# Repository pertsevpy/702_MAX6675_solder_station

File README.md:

# 702_MAX6675_solder_station
Simple 702 (Hakko 907) soldering station, use ATmega8 and MAX6675

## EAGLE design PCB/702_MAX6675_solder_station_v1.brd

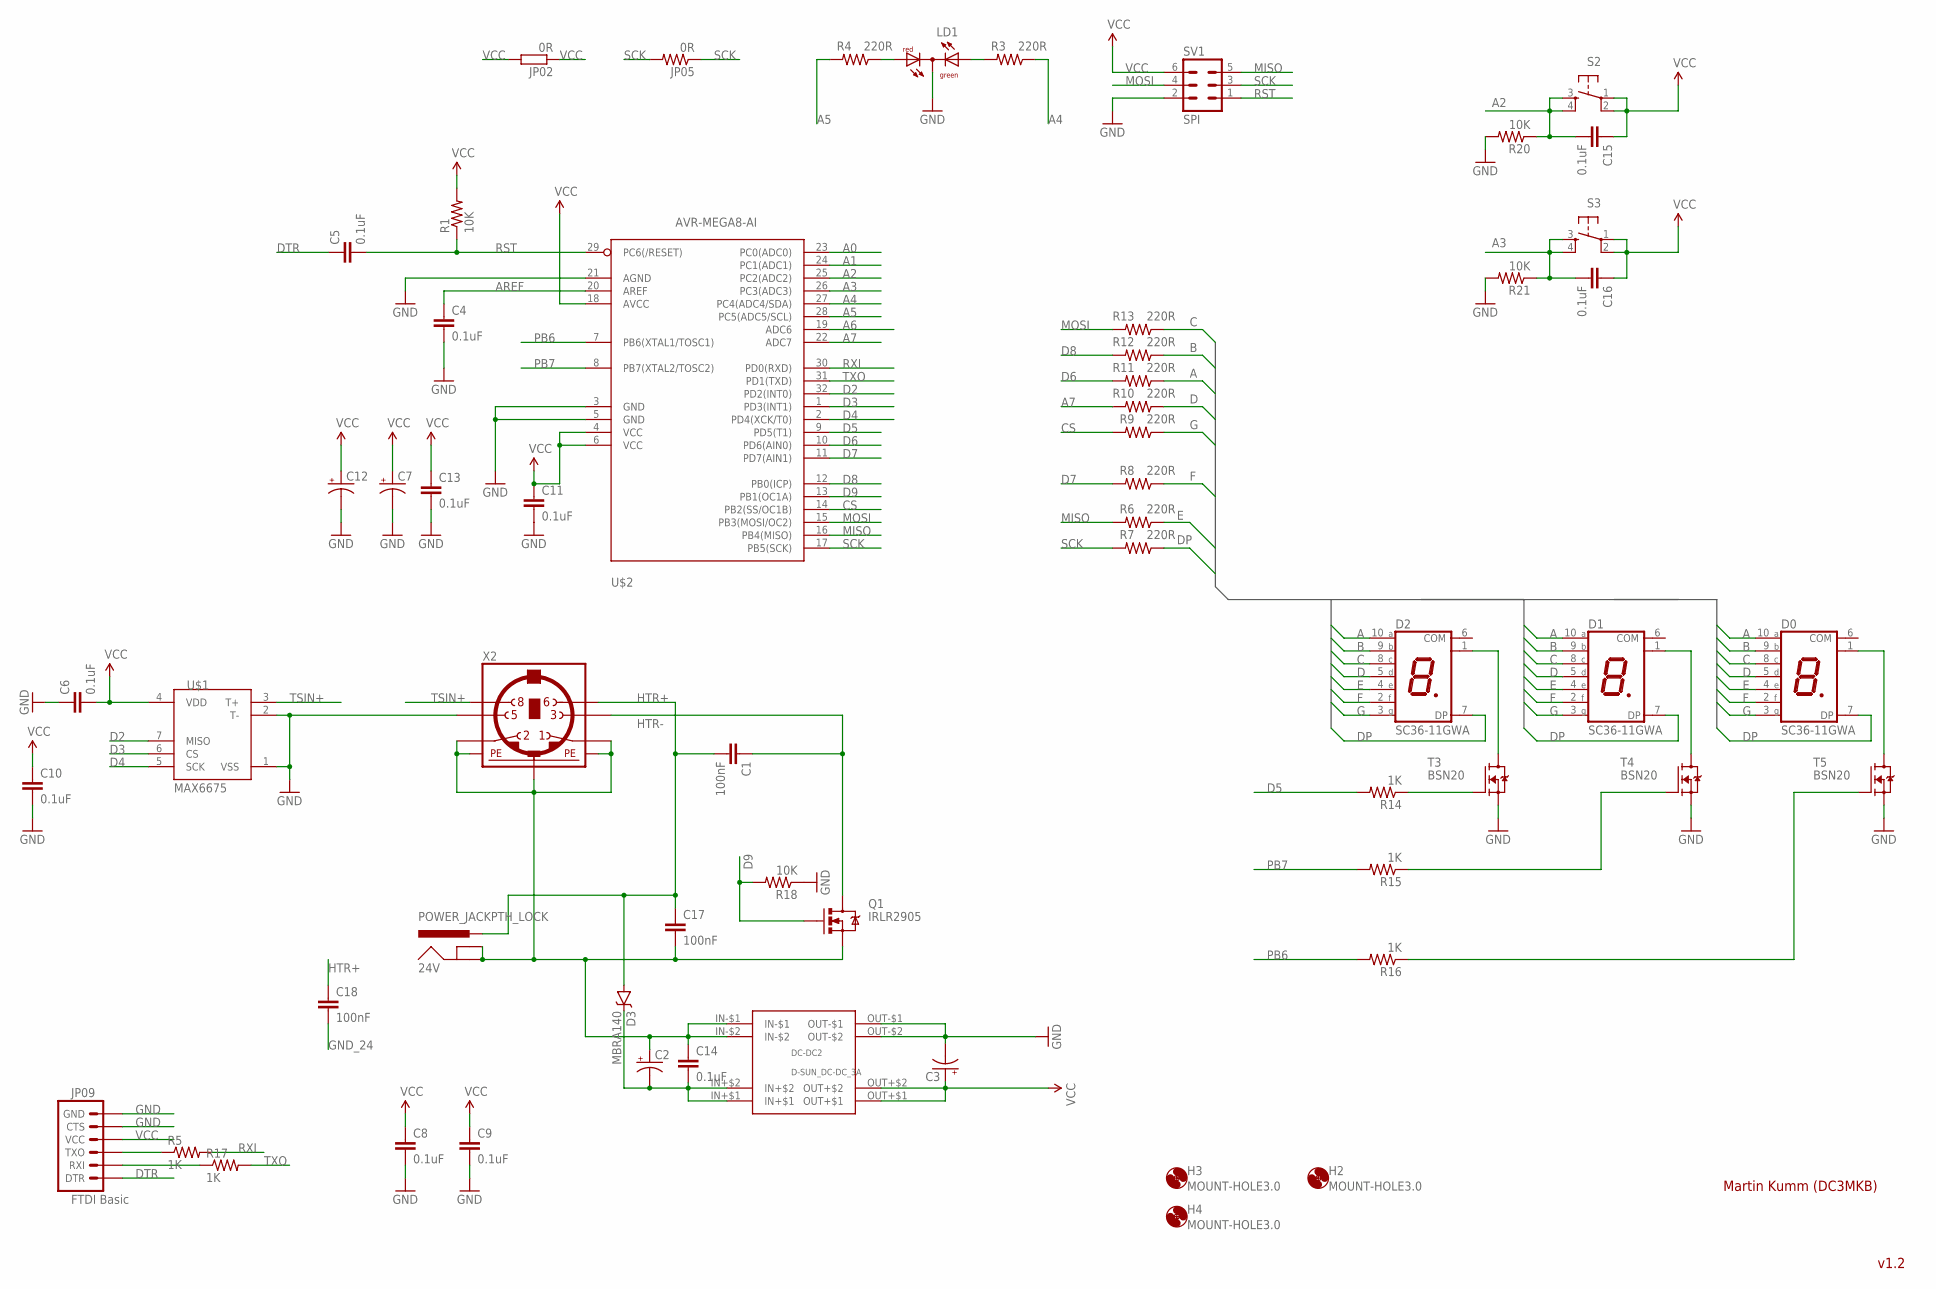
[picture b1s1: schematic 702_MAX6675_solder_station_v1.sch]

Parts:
24V: POWER_JACKPTH_LOCK; POWER_JACK_PTH_LOCK
C1, C17, C18: 100nF; 1206
C2, C3: CAP_POLPTH1; CPOL-RADIAL-100UF-25V
C4, C5, C6, C8, C9, C10, C11, C13, C15, C16: 0.1uF; 0805
C7, C12: CAP_POL1206; EIA3216
C14: 0.1uF; 1206
D0, D1, D2: SC36-11GWA; SA36-11GWA
D3: MBRA140; SMA-DIODE
DC-DC2: D-SUN_DC-DC_3A
H2, H3, H4: MOUNT-HOLE3.0; 3,0
JP02: 0R; R1206
JP05: 0R; 0805
JP09: FTDI Basic; 1X06
LD1: DUOLED-RG-C; DUOLED-C-5MM
Q1: IRLR2905; DPAK
R1, R18, R20, R21: 10K; 0805
R3, R4, R6, R7, R8, R9, R10, R11, R12, R13: 220R; 0805
R5, R14, R15, R16, R17: 1K; 0805
S2, S3: TAC_SWITCHPTH; TACTILE-PTH
SV1: SPI; ML6
T3, T4, T5: BSN20; SOT23
U$1: MAX6675; SO08-MAX6675
U$2: AVR-MEGA8-AI; TQFP32-08
X2: MINI_DIN_6; M_DIN6

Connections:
A: D0.10 (A), D1.10 (A), D2.10 (A), R11.1
A0: U$2.23 (PC0(ADC0))
A1: U$2.24 (PC1(ADC1))
A2: C15.2, R20.1, S2.3, S2.4, U$2.25 (PC2(ADC2))
A3: C16.2, R21.1, S3.3, S3.4, U$2.26 (PC3(ADC3))
A4: R3.1, U$2.27 (PC4(ADC4/SDA))
A5: R4.2, U$2.28 (PC5(ADC5/SCL))
A6: U$2.19 (ADC6)
A7: R10.2, U$2.22 (ADC7)
AREF: C4.1, U$2.20 (AREF)
B: D0.9 (B), D1.9 (B), D2.9 (B), R12.1
C: D0.8 (C), D1.8 (C), D2.8 (C), R13.1
CS: R9.2, U$2.14 (PB2(SS/OC1B))
D: D0.5 (D), D1.5 (D), D2.5 (D), R10.1
D2: U$1.7 (MISO), U$2.32 (PD2(INT0))
D3: U$1.6 (CS), U$2.1 (PD3(INT1))
D4: U$1.5 (SCK), U$2.2 (PD4(XCK/T0))
D5: R14.2, U$2.9 (PD5(T1))
D6: R11.2, U$2.10 (PD6(AIN0))
D7: R8.2, U$2.11 (PD7(AIN1))
D8: R12.2, U$2.12 (PB0(ICP))
D9: Q1.1 (G), R18.2, U$2.13 (PB1(OC1A))
DP: D0.7 (DP), D1.7 (DP), D2.7 (DP), R7.1
DTR: C5.1, JP09.1 (DTR)
E: D0.4 (E), D1.4 (E), D2.4 (E), R6.1
F: D0.2 (F), D1.2 (F), D2.2 (F), R8.1
G: D0.3 (G), D1.3 (G), D2.3 (G), R9.1
GND: C3.2 (-), C4.2, C6.1, C7.C (-), C8.2, C9.2, C10.2, C11.2, C12.C (-), C13.2, DC-DC2.OUT-$1, DC-DC2.OUT-$2, JP09.5 (CTS), JP09.6 (GND), LD1.C, R18.1, R20.2, R21.2, SV1.2, T3.2 (S), T4.2 (S), T5.2 (S), U$1.1 (VSS), U$1.2 (T-), U$2.3 (GND), U$2.5 (GND), U$2.21 (AGND), X2.5
GND_24: 24V.GND, 24V.GNDBREAK, C2.1 (+), C14.1, C17.2, C18.2, DC-DC2.IN-$1, DC-DC2.IN-$2, Q1.3 (S), X2.1, X2.2, X2.SH1 (PE1), X2.SH2 (PE2), X2.SH3 (PE3)
HTR+: 24V.PWR, C1.2, C17.1, C18.1, D3.A, X2.6
HTR-: C1.1, Q1.4 (D), X2.3
MISO: R6.2, SV1.5, U$2.16 (PB4(MISO))
MOSI: R13.2, SV1.4, U$2.15 (PB3(MOSI/OC2))
unnamed: LD1.AR, R4.1
unnamed: LD1.AX (AG), R3.2
unnamed: JP09.3 (TXO), R5.1
unnamed: D2.1 (COM), T3.3 (D)
unnamed: D0.1 (COM), T5.3 (D)
unnamed: JP09.2 (RXI), R17.1
unnamed: D1.1 (COM), T4.3 (D)
unnamed: R14.1, T3.1 (G)
unnamed: R15.1, T4.1 (G)
unnamed: R16.1, T5.1 (G)
unnamed: C2.2 (-), C14.2, D3.C, DC-DC2.IN+$1, DC-DC2.IN+$2
PB6: R16.2, U$2.7 (PB6(XTAL1/TOSC1))
PB7: R15.2, U$2.8 (PB7(XTAL2/TOSC2))
RST: C5.2, R1.1, SV1.1, U$2.29 (PC6(/RESET))
RXI: R5.2, U$2.30 (PD0(RXD))
SCK: JP05.1, JP05.2, R7.2, SV1.3, U$2.17 (PB5(SCK))
TSIN+: U$1.3 (T+), X2.8
TXO: R17.2, U$2.31 (PD1(TXD))
VCC: C3.1 (+), C6.2, C7.A (+), C8.1, C9.1, C10.1, C11.1, C12.A (+), C13.1, C15.1, C16.1, DC-DC2.OUT+$1, DC-DC2.OUT+$2, JP02.1, JP02.2, JP09.4 (VCC), R1.2, S2.1, S2.2, S3.1, S3.2, SV1.6, U$1.4 (VDD), U$2.4 (VCC), U$2.6 (VCC), U$2.18 (AVCC)

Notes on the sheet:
Martin Kumm (DC3MKB)
v1.2

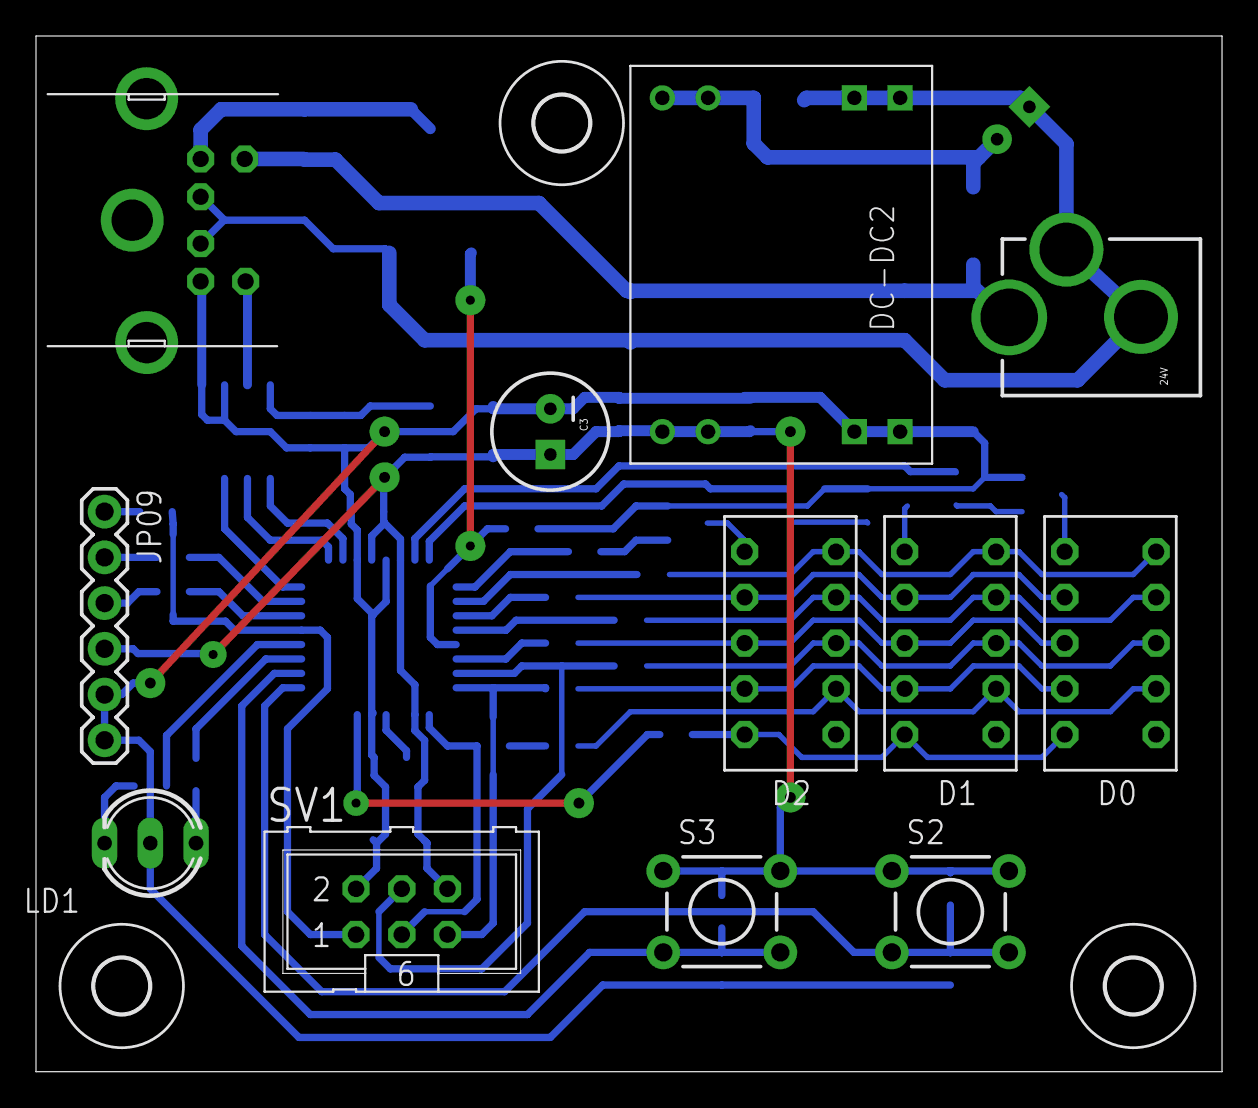
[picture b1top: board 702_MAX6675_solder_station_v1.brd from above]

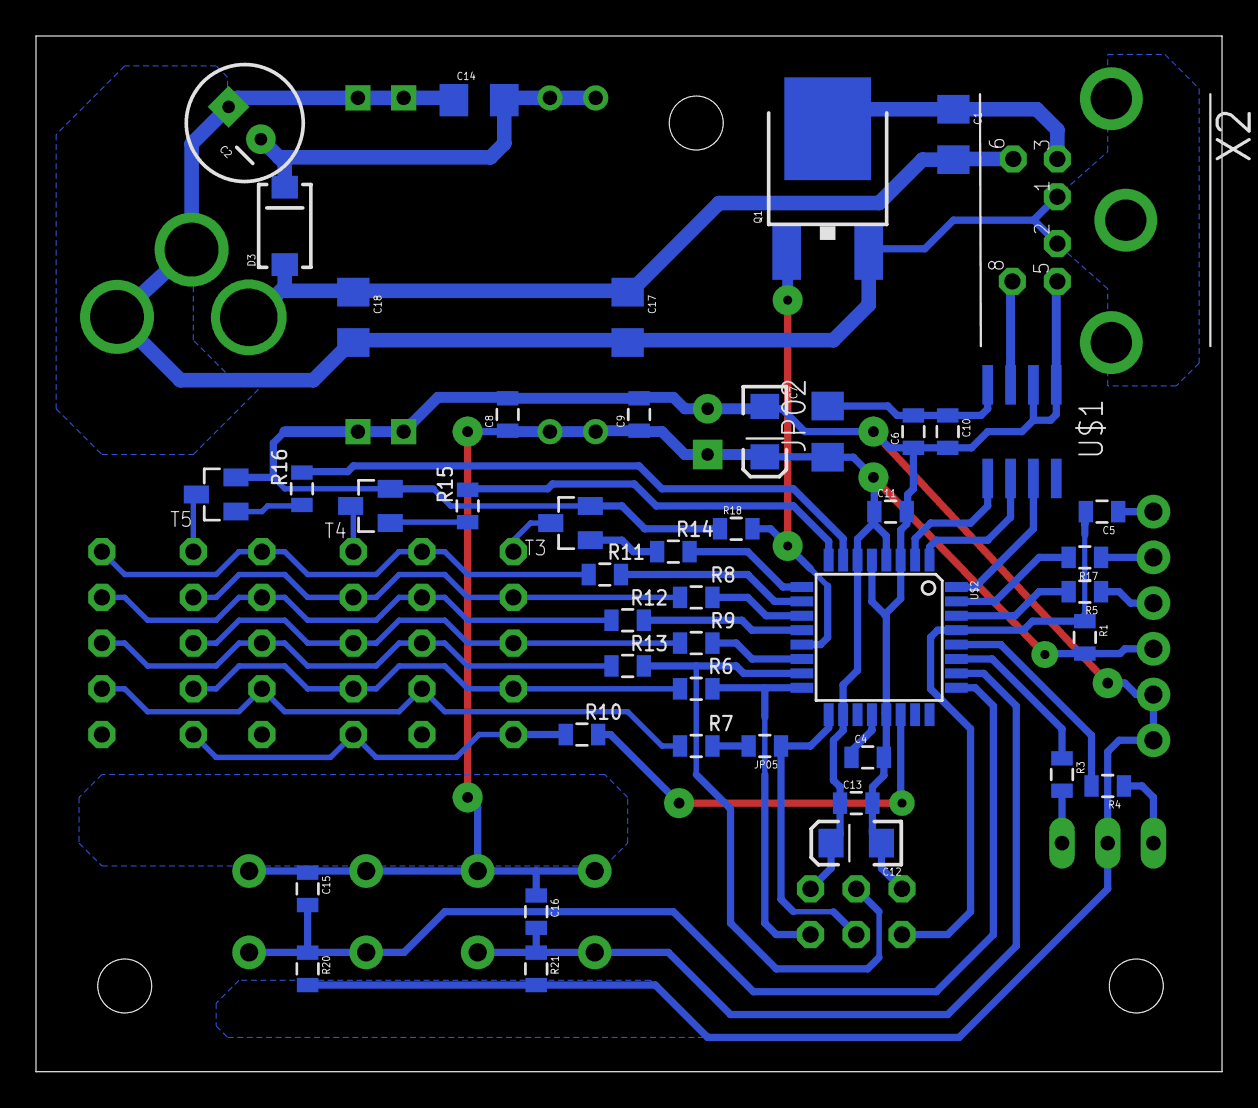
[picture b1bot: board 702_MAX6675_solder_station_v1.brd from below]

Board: 2 copper layers, 65.9 x 57.5 mm, 60 parts (46 on the bottom side), 49 nets.

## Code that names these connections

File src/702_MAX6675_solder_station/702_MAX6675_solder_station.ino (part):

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#define SERIAL_DEBUG_INTERVAL_MS 1000

// Pin definitions
#define BTN_LEFT_PIN   PC3  // PC3 (ADC3) A3
#define BTN_RIGHT_PIN  PC2  // PC2 (ADC2) A2
#define HEATER_PIN     PB1  // D9
#define GREEN_LED_PIN  PC5  // PC5 (ADC5/SCL)
#define RED_LED_PIN    PC4  // PC4 (ADC4/SDA)

// MAX6675 pins
#define MISO_PIN PD2
#define CS_PIN   PD3
#define SCLK_PIN PD4

// 7-segment display segment pins
#define PIN_7SEG_A  PD6  // 6
#define PIN_7SEG_B  PB0  // 8
#define PIN_7SEG_C  PB3  // 11
#define PIN_7SEG_D  PC0  // A0
#define PIN_7SEG_E  PB4  // 12
#define PIN_7SEG_F  PD7  // 7
#define PIN_7SEG_G  PB2  // 10
#define PIN_7SEG_DP PB5  // 13

// 7-segment display digit select pins
#define PIN_7SEG_ACT_LEFT   PD5  // D5
#define PIN_7SEG_ACT_MIDDLE PB7  // PORTB7 (XTAL2)
#define PIN_7SEG_ACT_RIGHT  PB6  // PORTB6 (XTAL1)

// Bit manipulation macros
#define SET_BIT(port, pin)    ((port) |= (1 << (pin)))
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
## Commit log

2026-01-09 Add Eagle Cad PCB files
2026-01-09 Add source code

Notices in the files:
parts and their libraries:
SparkFun-Connectors: Licensing: Creative Commons ShareAlike 4.0 International - https://creativecommons.org/licenses/by-sa/4.0
